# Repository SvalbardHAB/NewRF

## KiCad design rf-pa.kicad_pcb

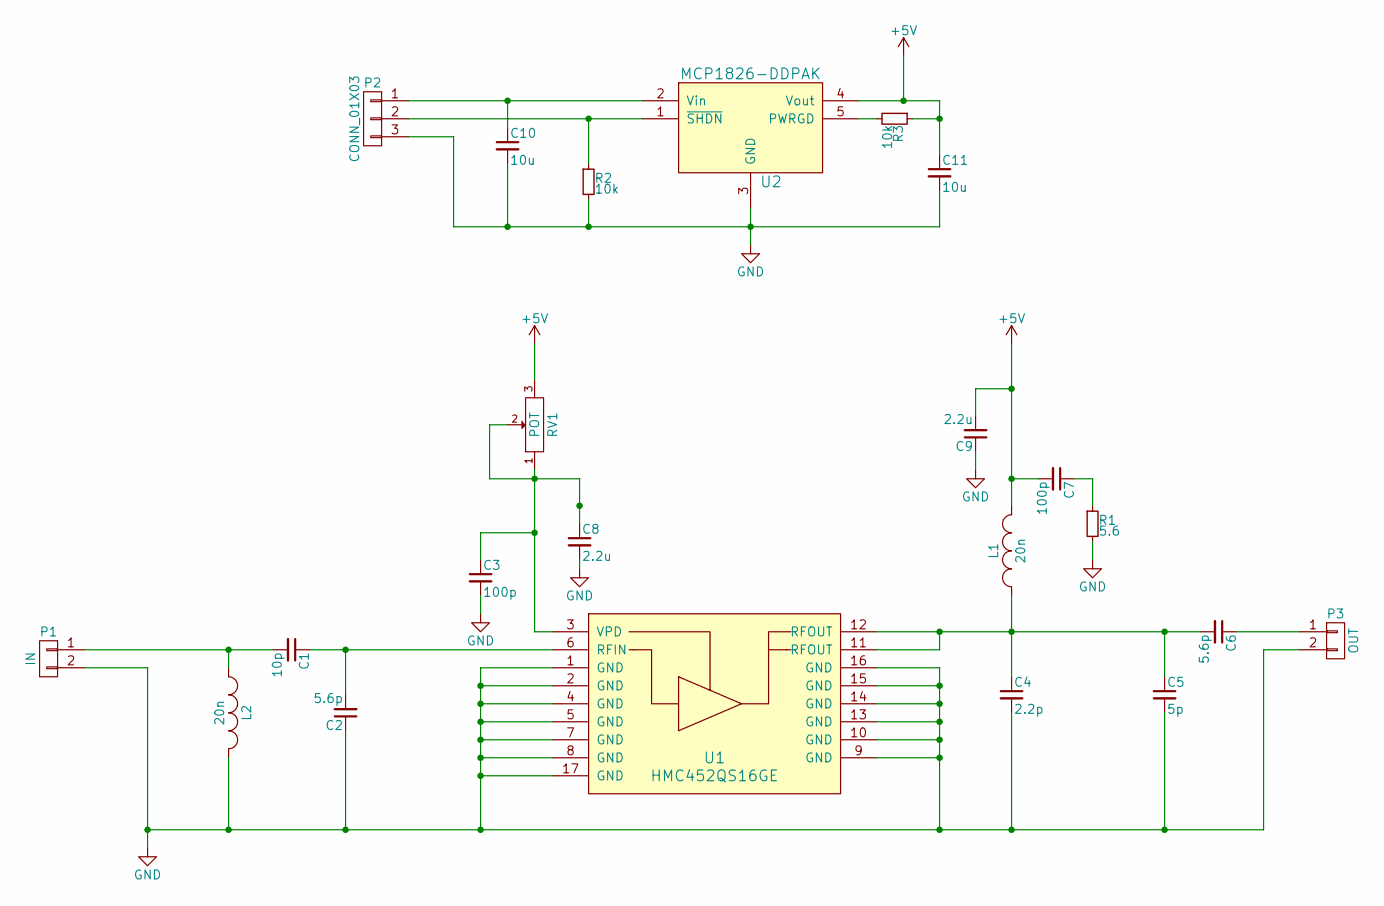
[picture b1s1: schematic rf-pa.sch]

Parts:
C1: 10p; C_0402
C2, C6: 5.6p; C_0402
C3, C7: 100p; C_0402
C4: 2.2p; C_0402
C5: 5p; C_0402
C8, C9: 2.2u; C_0603
C10, C11: 10u; C_1206
L1, L2: 20n; R_0402
P1: IN; RFcon
P2: CONN_01X03; Pin_Header_Straight_1x03
P3: OUT; RFcon
R1: 5.6; R_0402
R2, R3: 10k; R_0402
RV1: POT; Potentiometer_Trimmer-Suntan-TSR-3386P
U1: HMC452QS16GE; QSOP-16EP_3.9x4.9mm_Pitch0.635mm
U2: MCP1826-DDPAK; TO-263-5Lead

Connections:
+5V: C7.2, C9.2, C11.1, L1.2, R3.1, RV1.3, U2.4 (Vout)
GND: C2.1, C3.2, C4.2, C5.2, C8.2, C9.1, C10.2, C11.2, L2.2, P1.2, P2.3, P3.2, R1.2, R2.2, U1.1 (GND), U1.2 (GND), U1.4 (GND), U1.5 (GND), U1.7 (GND), U1.8 (GND), U1.9 (GND), U1.10 (GND), U1.13 (GND), U1.14 (GND), U1.15 (GND), U1.16 (GND), U1.17 (GND), U2.3 (GND)
unnamed: C1.1, C2.2, U1.6 (RFIN)
unnamed: C1.2, L2.1, P1.1
unnamed: C3.1, C8.1, RV1.1, RV1.2, U1.3 (VPD)
unnamed: C4.1, C5.1, C6.2, L1.1, U1.11 (RFOUT), U1.12 (RFOUT)
unnamed: C6.1, P3.1
unnamed: C7.1, R1.1
unnamed: C10.1, P2.1, U2.2 (Vin)
unnamed: P2.2, R2.1, U2.1 (~SHDN)
unnamed: R3.2, U2.5 (PWRGD)

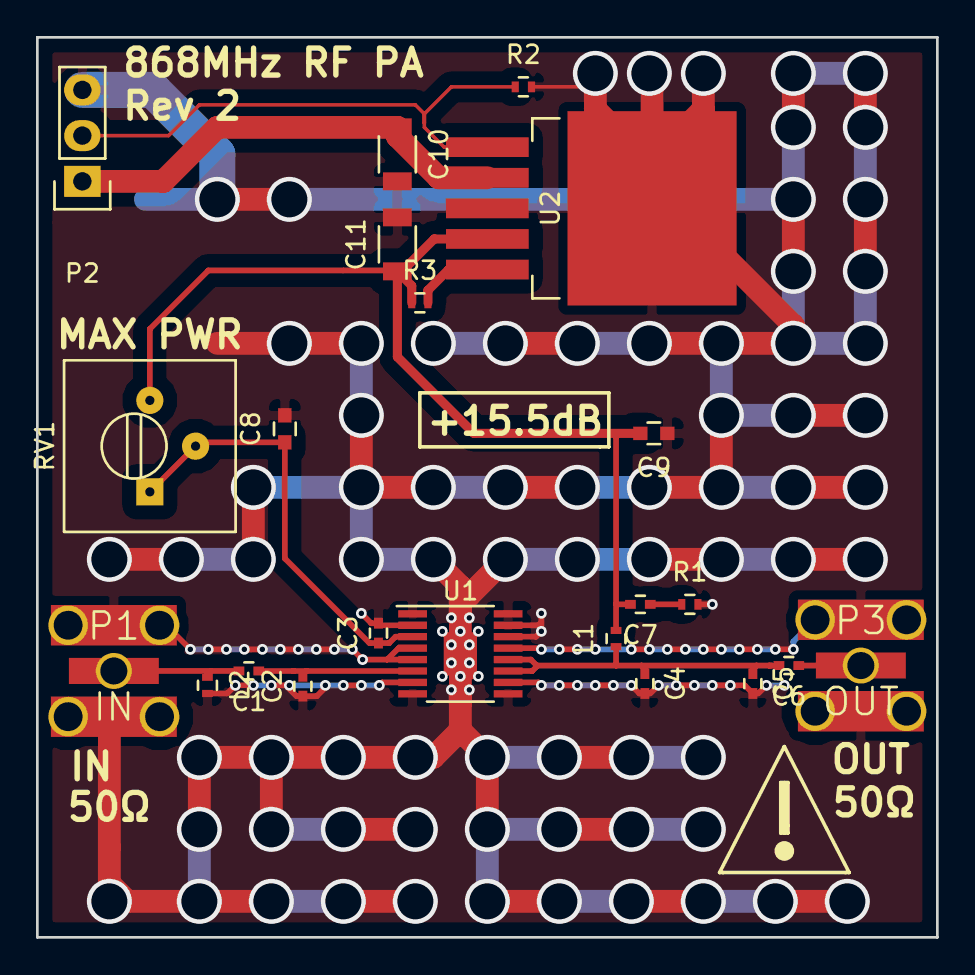
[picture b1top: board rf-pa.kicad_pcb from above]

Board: 4 copper layers, 50.0 x 50.0 mm, 22 parts (0 on the bottom side), 11 nets.

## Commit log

2016-07-04 Design for new RF PA
